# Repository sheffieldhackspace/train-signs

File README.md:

# Train Station Clocks

The clocks in the space. See also Nottingham Hackspace's wiki:

<https://wiki.nottinghack.org.uk/wiki/BigClocks>

## Hardware

The microcontroller is a Seeed Studio XIAO ESP32C3. For hardware details, schematic, and PCB layout, see the [AEGMIS_GV60 repository](https://github.com/sheffieldhackspace/AEGMIS_GV60).

## Running the project

### Prerequisites

* [PlatformIO](https://platformio.org/) installed

### Installation

Flash the server environment to the device:

```bash
$ pio run -t clean -t upload -e aegmis
```

To run on an SSD1306 OLED display instead, use the `oled` environment:

```bash
$ pio run -t clean -t upload -e oled
```

For wiring the OLED, connect it to the XIAO ESP32C3 as follows:

| SSD1306 | XIAO ESP32C3 |
|---------|--------------|
| VCC     | 3V3          |
| GND     | GND          |
| SDA     | D4           |
| SCL     | D5           |

### Generation of compatible image data

```bash
$ ./icons/image2bytes.py ./icons/skull.gif
```

### Setting the status of the display

Once flashed, the display will show its IP address. You can then control it via HTTP:

```bash
$ curl http://ip_address:port/ --data '{
  "text": "Repair cafe @\nSheffield Hackspace",
  "text_size": 1,
  "text_wrap": true,
  "flashing": false,
  "inverted": false,
  "horizontal_align": "left",
  "vertical_align": "top",
  "image": "ABgAAZmAAf+AGf+YH//4DgAwDv/wfH/+fv+uP/UEP1VU8VF39xV/MVX8PV/8cf++f/8eD/+wDgAwH//4Gf+YAf+AAZmAABgA",
  "image_width": 24,
  "image_height": 24
}'
```

| Parameter | Type | Default | Description |
|-----------|------|---------|-------------|
| `text` | string | `""` | The text to display. If too long, the display will scroll it. |
| `text_size` | integer | `1` | Text size multiplier, 1–5. |
| `text_wrap` | boolean | `true` | If true, overflow scrolls vertically; if false, horizontally. |
| `flashing` | boolean | `false` | If true, inverts colours every second producing a flashing animation. |
| `inverted` | boolean | `false` | Invert the colours of the display. |
| `speed` | integer | `5` | Scroll speed. |
| `horizontal_align` | string | `"left"` | `"left"`, `"center"`, `"right"`. |
| `vertical_align` | string | `"top"` | `"top"`, `"middle"`, `"bottom"`. |
| `image` | string | `""` | Base64-encoded image (output of the image2bytes script). |
| `image_width` | integer | `0` | Image width in pixels. |
| `image_height` | integer | `0` | Image height in pixels. |

### Integration tests

A test script is included that sends a series of curl requests and prompts you to verify each result visually:

```bash
$ chmod +x integration-test.sh && ./integration-test.sh 192.168.1.100
```

### Included libraries

* Adafruit GFX Library - The base for our implementation
* [AEGMIS_GV60](https://github.com/sheffieldhackspace/AEGMIS_GV60) - Provides an Adafruit GFX compatible driver for the train sign display; based on the reverse engineering work of [`daniel1111`](https://github.com/daniel1111/BigClockSnake) from the Nottingham Hackspace
* DotWidget - Provides a standard way of building a display widget for small IoT screens

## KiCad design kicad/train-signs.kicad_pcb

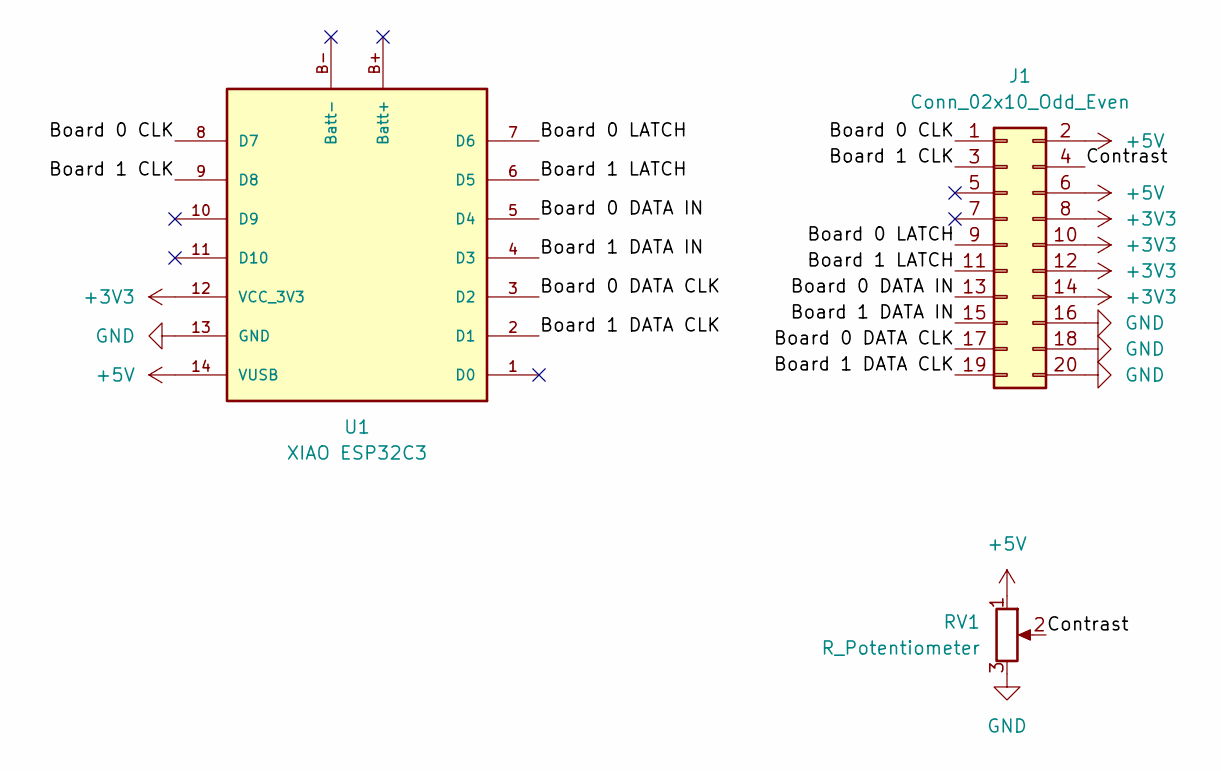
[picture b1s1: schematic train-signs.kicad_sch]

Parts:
J1: Conn_02x10_Odd_Even; IDC-Header_2x10_P2.54mm_Vertical
RV1: R_Potentiometer; Potentiometer_Taiwan_Alpha_9mm_Vertical
U1: XIAO ESP32C3; XIAO Seeed ESP32C3 DIP

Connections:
+3V3: J1.8, J1.10, J1.12, J1.14, U1.12 (VCC_3V3)
+5V: J1.2, J1.6, RV1.1, U1.14 (VUSB)
/Board 0 CLK: J1.1, U1.8 (D7)
/Board 0 DATA CLK: J1.17, U1.3 (D2)
/Board 0 DATA IN: J1.13, U1.5 (D4)
/Board 0 LATCH: J1.9, U1.7 (D6)
/Board 1 CLK: J1.3, U1.9 (D8)
/Board 1 DATA CLK: J1.19, U1.2 (D1)
/Board 1 DATA IN: J1.15, U1.4 (D3)
/Board 1 LATCH: J1.11, U1.6 (D5)
/Contrast: J1.4, RV1.2
GND: J1.16, J1.18, J1.20, RV1.3, U1.13 (GND)

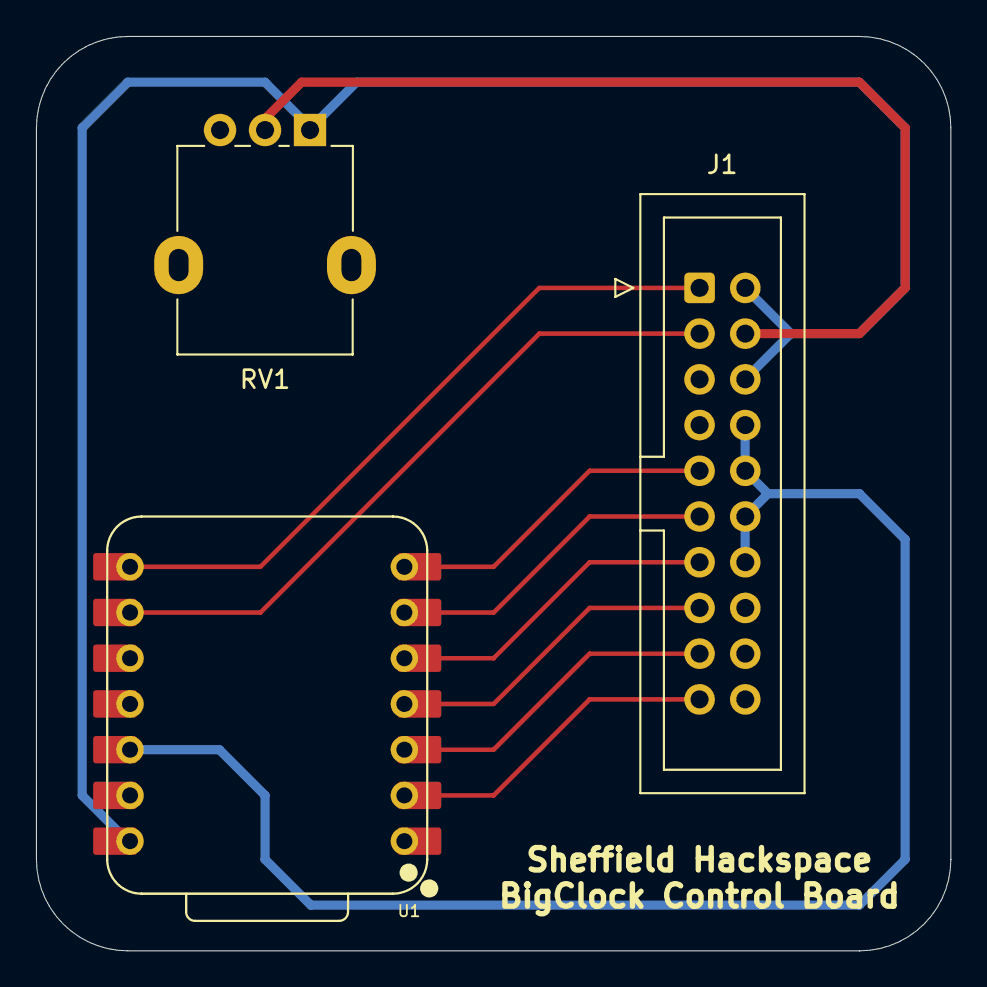
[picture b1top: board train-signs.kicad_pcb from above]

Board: 2 copper layers, 50.8 x 50.8 mm, 3 parts (0 on the bottom side), 12 nets.

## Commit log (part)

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2024-03-09 add images
2024-03-14 add platformio and libraries
2024-03-14 move and rename libraries
2024-03-14 include arduino and change text (to test)
2024-03-14 move big clock library
2024-03-14 include adafruit I2Cdevice (complains if not)
2024-03-14 update text to scroll around screen
2024-03-14 add animated jif
2024-03-18 add other demo files
2024-06-10 add baud rate to ini file
2024-06-11 add ESP8266 Timer Interrupt library
2024-06-11 add build environment for d1 mini and interrupt test script
2024-06-11 use ESP interrupt in BigClock if available
2024-06-11 define PINS in BigClock so they can be changed
2025-10-20 change to pio env
2025-10-25 update readme and add pin layout
2025-10-25 add W5500 Ethernet library
2025-10-25 change clock latch pin to pin 5 (conflict with Ethernet SD card pin 4)
2025-10-25 change SPI to use transactions (Ethernet SPI settings are different so should not conflict)
2025-10-25 add ethernet script (not working while sign is enabled)
2025-11-16 add `before`/`after` functions to reset SPI settings for Ethernet shield
2025-11-16 update messages
2025-11-16 only one message
2025-11-16 accept and respond to HTTP requests via curl only at the moment (no form data)
2025-11-16 add image printing (needs more memory for full screen)
2025-11-16 temporary limit image width/height to 32/20 until better memory management
2025-11-30 add example images to use
2026-01-14 simplification of the output method
2026-01-14 move the output method lower to reflect the abstraction layers
2026-01-14 Remove unused flag
2026-01-14 Redundant code
2026-01-14 This is no longer needed, perhaps because I rewrote the loops in the output method
2026-01-14 Match the board numbers with the board selector values
2026-01-14 Calculate the row_start inside the output_segment method
2026-01-14 proper use of board constants
2026-01-14 set bw pixels throughout the loop
2026-01-14 Big clock cleanup (#2)
    * simplification of the output method
    * move the output method lower to reflect the abstraction layers
    * Remove unused flag
    * Redundant code
    * This is no longer needed, perhaps because I rewrote the loops in the output method
    * Match the board numbers with the board selector values
2026-01-15 Rewrite the output generator
2026-01-15 Rewrite the output generator (#3)
2026-01-15 Refactor: method signature consistency
2026-01-15 Refactor: method signature consistency (#4)
2026-01-15 Big clock cleanup
2026-01-15 Big clock cleanup (#5)
2026-01-15 Improved refresh with less flickering
2026-01-16 SoftSPI
2026-01-17 Remove TimerOne clone
2026-01-18 Migration to Arduino Nano ESP32
2026-01-18 Migration to Arduino Nano ESP32 (#6)
    * SoftSPI
    * Remove TimerOne clone
    * Migration to Arduino Nano ESP32
    ---------
2026-01-18 Empty folder cleanup
2026-01-18 KiCAD schema
2026-01-18 KiCAD schema (#7)
2026-01-18 Separate lines for top and bottom board
2026-01-18 Correct KiCAD schema
2026-01-18 Use DFU instead of esptool
2026-01-19 Use libraries via platformio registry
2026-01-19 Remove old files
2026-01-19 Remove library information from README
2026-01-31 WiFi server
2026-01-31 Custom font
2026-01-31 Displays the last message received via HTTP
2026-01-31 Rotate every 5 seconds between the last 10 messages
2026-01-31 Pass the framebuffer in the initializer of the BigClock display
2026-01-31 Refactor magic numbers
2026-01-31 Information about the SSID it is connected to as a base message
2026-01-31 Refactor record initialisation
2026-01-31 Display the newest message as it arrives, and then go backwards
2026-01-31 cleanup of the sources
2026-01-31 Add MessageQueue class
2026-01-31 Move scope of the variables
2026-01-31 Better font
2026-01-31 Org01Condensed - a modification of the Org_01 font
2026-02-01 Message scroll
2026-02-01 Remove the queue
2026-02-01 Simplified HTTP_SEPARATOR finding JsonDocument in request
2026-02-01 Message speed and background color configurable via JSON
2026-02-01 alignv
2026-02-01 Unused library
2026-02-01 Simplify method definition
2026-02-01 Remove unused pin from the board definition
2026-02-01 Scroll bugfix
2026-02-02 Use C++ setters
2026-02-02 Remove redundant configuration
2026-02-10 Migrate to XIAO Studio Seeed ESP32C6
2026-02-10 Reformat using CLion
2026-02-10 Update the schematic with XIAO Seeed ESP32C3 and build a PCB
2026-02-10 Add an enum for vertical alignbment
2026-02-10 Refactor the BigBoard class
2026-02-10 Drop SoftSPI library in favour of SPI implementation from Adafruit GFX
2026-02-10 Adafruit_BigClock as a graphic interface for the BigClock
2026-02-10 Single line strings
2026-02-10 Pass pins to the callback function
2026-02-10 Migrate board display into the driver
2026-02-10 Migrate segment display into the driver
2026-02-11 Adafruit_BigClockSPI as an SPI device interface for the BigClock
2026-02-11 Expose methods for setting keepalive and latch pins state
2026-02-11 Refactor attribute name
2026-02-11 Migrate to XIAO Studio Seeed ESP32C3
2026-02-11 Cleanup the example code
2026-02-11 Refactor the constant names
2026-02-11 Introduce the Widget class for hackspace display
2026-02-11 Reintroduce the display inverting
2026-02-11 Introduce text alignment
2026-02-11 Implement horizontal scrolling
2026-02-11 Add text_wrap setting
2026-02-11 Remove modified fonts
2026-02-12 Text align
2026-02-12 Text wrapping informs the scroll direction
2026-02-12 Refactor scroll to one method
2026-02-12 Pass the coordinates to printMessage
2026-02-12 Refactor align to one method
2026-02-12 Correct the text align when horizontal scrolling
2026-02-12 Move magic number to a definition
2026-02-12 Add flash
2026-02-12 Add crude image support
2026-02-12 Image + text scrolling in both directions
2026-02-12 Separate display driver from the widget library
2026-02-13 Image follows text alignment
2026-02-13 nitpick
2026-02-13 Refactor the apply methods
2026-02-13 Refactored naming consistency
2026-02-13 Pass the image dimensions alongside the image
2026-02-13 Align the image vertically when in horizontal scroll mode
2026-02-13 Separate the widget library from the driver library
2026-02-15 Simplify the python script for converting images
2026-02-15 Update the README
2026-02-19 Pinout to match what I did on the perfboard
2026-02-21 add pixel logo ;]
2026-02-22 Return 200 response on a successful request
2026-02-23 Put things in stack and global and not in the heap
2026-02-23 Limit the payload to at most 4kB
2026-02-23 SERVER_PORT + RESPONSE_400 + deserializeJson error handling
2026-02-23 Allow for running the server at home with an SSD1306 OLED display
2026-02-23 Correct JSON format in the README.md
2026-02-23 Add a nicer photo for the prototype
2026-02-24 Upgrade to gnu++17
2026-02-24 Rename libraries not to get in trouble
2026-02-24 Proper memory allocation for the global objects
2026-02-24 Address some CTidy warnings
2026-02-24 Modernize the widget
2026-02-24 Memory management improvements
2026-02-24 Rename flash to flashing
2026-02-24 Rename invert to inverted
2026-02-24 Rename flash to updateFlash
2026-02-24 Privatize some methods
2026-02-24 Add a destructor
2026-02-24 Move implementation to cpp
2026-02-24 Move image type casting into a different place
2026-02-25 Pre-render the text
2026-02-25 Refactor names and optimise text rendering
2026-02-25 Use isEmpty() instead of == ""
2026-02-25 Font setting outside of the widget
2026-02-25 Add Credentials.h.example
2026-02-25 Set things in the correct order
2026-02-26 Font parameter and drawVisible method
2026-02-26 Update readme files
2026-02-26 Move the AEGMIS_GV60 library out of the repository
2026-02-26 Correct environment for the AEGMIS
2026-02-26 text_size instead of font
2026-02-27 Extract image drawing into a separate class
2026-02-27 First version of DotText
2026-02-27 Remove the drawVisible method
2026-02-27 Second version of DotText
2026-02-28 Introduce DotElement class
2026-02-28 First version of DotContainer
2026-02-28 Use DotContainer in DotWidget
2026-02-28 Introduce new alignment logic
2026-02-28 Introduce integration tests
2026-02-28 DotText is really just a DotVertical container
2026-03-01 add padded logo ;]
